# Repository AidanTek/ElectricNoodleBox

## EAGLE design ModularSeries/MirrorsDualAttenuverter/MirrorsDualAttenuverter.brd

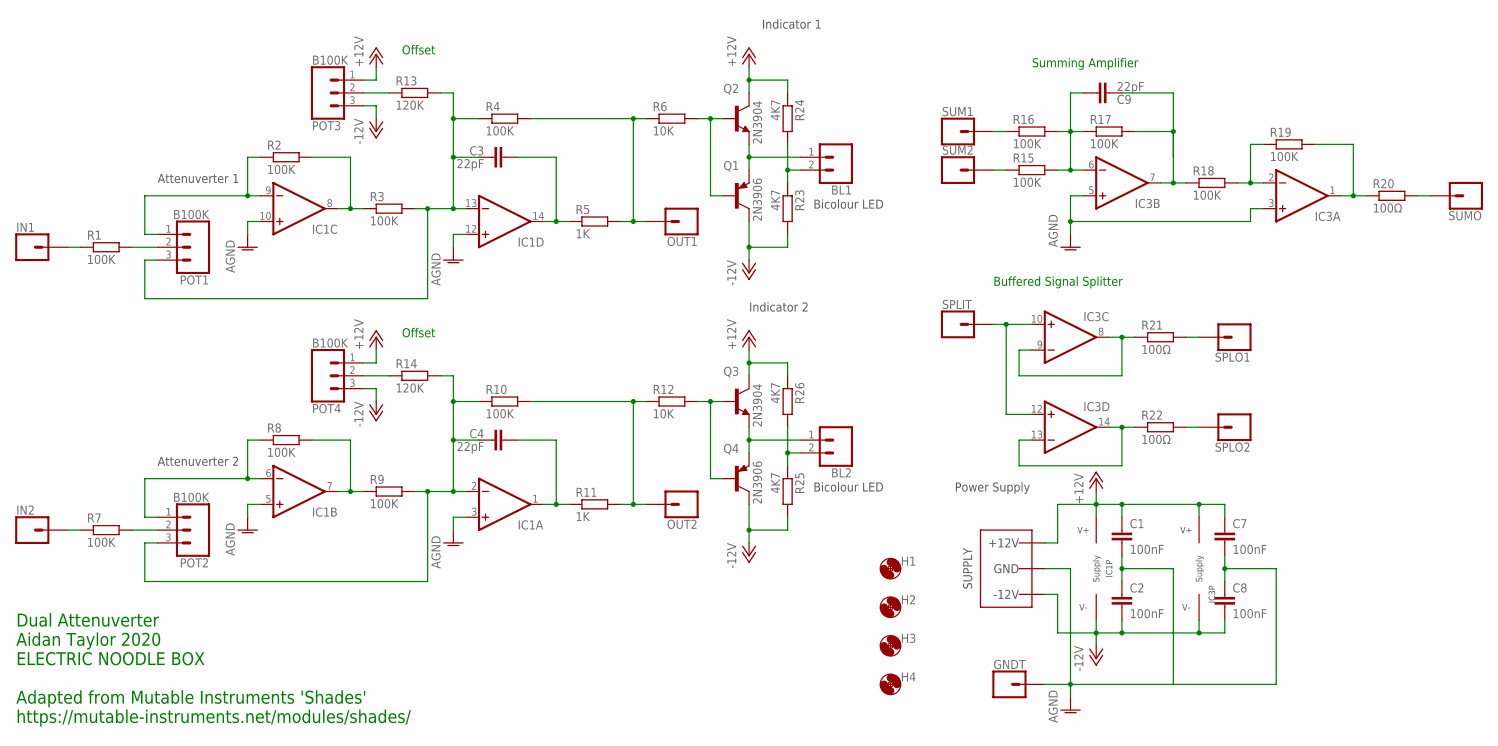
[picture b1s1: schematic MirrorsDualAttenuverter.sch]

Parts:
BL1, BL2: 2XWIREPAD; 1X02
C1, C2, C7, C8: 100nF; C050-025X075
C3, C4, C9: 22pF; C050-025X075
GNDT: 1XWIREPAD; 1X01
H1, H2, H3, H4: MOUNT-HOLE3.2; 3,2
IC1, IC3: TL0X4DIL; DIL14
IN1, IN2: 1XWIREPAD; 1X01
OUT1, OUT2: 1XWIREPAD; 1X01
POT1, POT2, POT3, POT4: B100K; 1X03
Q1, Q4: 2N3906; TO92
Q2, Q3: 2N3904; TO92
R1, R2, R3, R4, R7, R8, R9, R10, R15, R16, R17, R18, R19: 100K; 0207/10
R5, R11: 1K; 0207/10
R6, R12: 10K; 0207/10
R13, R14: 120K; 0207/10
R20, R21, R22: 100Ω; 0207/10
R23, R24, R25, R26: 4K7; 0207/10
SPLIT: 1XWIREPAD; 1X01
SPLO1, SPLO2: 1XWIREPAD; 1X01
SUM1, SUM2: 1XWIREPAD; 1X01
SUMO: 1XWIREPAD; 1X01
WP1: COMBO_SUPPLY_HEADER; COMBINED_POWER

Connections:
+12V: C1.1, C7.1, IC1.4 (V+), IC3.4 (V+), POT3.1, POT4.1, Q2.1 (C), Q3.1 (C), R24.1, R26.1, WP1.V+1 (V++), WP1.V+2 (V++), WP1.V+3 (V++)
-12V: C2.2, C8.2, IC1.11 (V-), IC3.11 (V-), POT3.3, POT4.3, Q1.1 (C), Q4.1 (C), R23.2, R25.2, WP1.V-1 (V--), WP1.V-2 (V--), WP1.V-3 (V--)
AGND: C1.2, C2.1, C7.2, C8.1, GNDT.1, IC1.3 (+IN), IC1.5 (+IN), IC1.10 (+IN), IC1.12 (+IN), IC3.3 (+IN), IC3.5 (+IN), WP1.GND1 (AGND), WP1.GND2 (AGND), WP1.GND3 (AGND), WP1.GND4 (AGND), WP1.GND5 (AGND), WP1.GND6 (AGND), WP1.GND7 (AGND), WP1.GND8 (AGND)
unnamed: POT1.2, R1.2
unnamed: IC1.9 (-IN), POT1.1, R2.1
unnamed: POT2.2, R7.2
unnamed: IC1.8 (OUT), R2.2, R3.1
unnamed: C3.1, IC1.13 (-IN), POT1.3, R3.2, R4.1, R13.2
unnamed: OUT1.1, R4.2, R5.2, R6.1
unnamed: C3.2, IC1.14 (OUT), R5.1
unnamed: Q1.2 (B), Q2.2 (B), R6.2
unnamed: IN1.1, R1.1
unnamed: IC3.2 (-IN), R18.2, R19.1
unnamed: IC1.6 (-IN), POT2.1, R8.1
unnamed: IC1.7 (OUT), R8.2, R9.1
unnamed: C4.1, IC1.2 (-IN), POT2.3, R9.2, R10.1, R14.2
unnamed: OUT2.1, R10.2, R11.2, R12.1
unnamed: C4.2, IC1.1 (OUT), R11.1
unnamed: IN2.1, R7.1
unnamed: Q3.2 (B), Q4.2 (B), R12.2
unnamed: BL2.1, Q3.3 (E), Q4.3 (E)
unnamed: BL1.1, Q1.3 (E), Q2.3 (E)
unnamed: POT3.2, R13.1
unnamed: C9.2, IC3.6 (-IN), R15.2, R16.2, R17.1
unnamed: POT4.2, R14.1
unnamed: C9.1, IC3.7 (OUT), R17.2, R18.1
unnamed: IC3.1 (OUT), R19.2, R20.1
unnamed: R20.2, SUMO.1
unnamed: R16.1, SUM1.1
unnamed: R15.1, SUM2.1
unnamed: IC3.8 (OUT), IC3.9 (-IN), R21.1
unnamed: IC3.13 (-IN), IC3.14 (OUT), R22.1
unnamed: IC3.10 (+IN), IC3.12 (+IN), SPLIT.1
unnamed: R21.2, SPLO1.1
unnamed: R22.2, SPLO2.1
unnamed: BL1.2, R23.1, R24.2
unnamed: BL2.2, R25.1, R26.2

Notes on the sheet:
Power Supply
Attenuverter 1
Attenuverter 2
Indicator 1
Indicator 2
Bicolour LED
Dual Attenuverter Aidan Taylor 2020 ELECTRIC NOODLE BOX Adapted from Mutable Instruments 'Shades' https://mutable-instruments.net/modules/shades/
Offset
Summing Amplifier
Buffered Signal Splitter

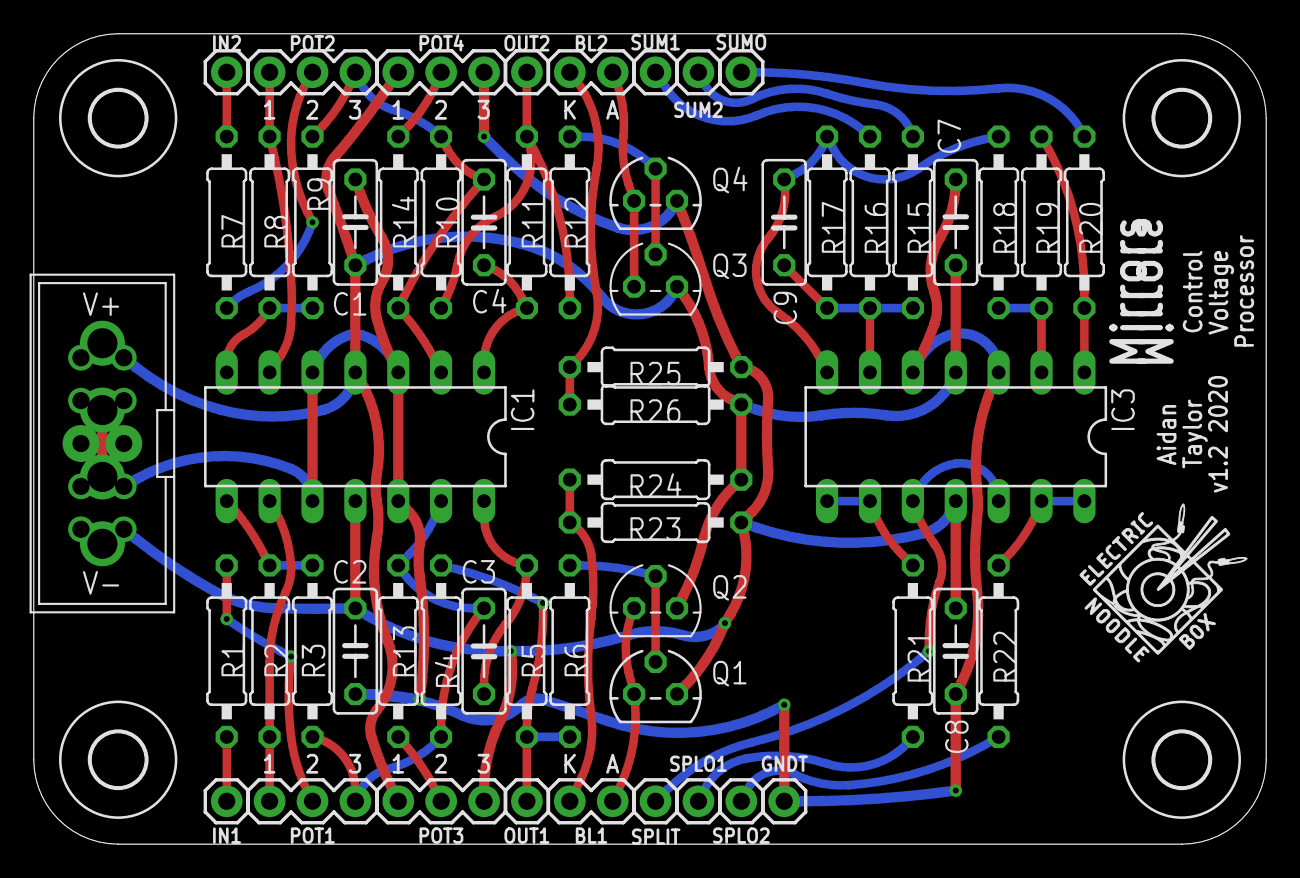
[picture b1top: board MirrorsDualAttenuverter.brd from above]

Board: 2 copper layers, 73.0 x 48.0 mm, 63 parts (1 on the bottom side), 37 nets.

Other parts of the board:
U$1, U$2: LOGO10X10

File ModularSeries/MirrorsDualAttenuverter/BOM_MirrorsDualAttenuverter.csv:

"Qty";"Value";"Device";"Package";"Parts";"Description";"POPULARITY";"SPICEPREFIX";
"2";"";"TL0X4DIL";"DIL14";"IC1, IC3";"";"";"";
"15";"100K";"R-EU_0207/10";"0207/10";"R1, R2, R3, R4, R7, R8, R9, R10, R13, R14, R15, R16, R17, R18, R19";"RESISTOR, European symbol";"81";"R";
"6";"100nF";"C-EU050-025X075";"C050-025X075";"C1, C2, C5, C6, C7, C8";"CAPACITOR, European symbol";"29";"C";
"3";"100Ω";"R-EU_0207/10";"0207/10";"R20, R21, R22";"RESISTOR, European symbol";"81";"R";
"4";"1K";"R-EU_0207/10";"0207/10";"R5, R6, R11, R12";"RESISTOR, European symbol";"81";"R";
"11";"1XWIREPAD";"1XWIREPAD";"1X01";"GNDT, IN1, IN2, OUT1, OUT2, SPLIT, SPLO1, SPLO2, SUM1, SUM2, SUMO";"";"";"";
"3";"22pF";"C-EU050-025X075";"C050-025X075";"C3, C4, C9";"CAPACITOR, European symbol";"29";"C";
"2";"2XWIREPAD";"2XWIREPAD";"1X02";"BL1, BL2";"";"";"";
"4";"B100K";"3XWIREPAD";"1X03";"POT1, POT2, POT3, POT4";"";"";"";
"1";"COMBO_SUPPLY_HEADER";"COMBO_SUPPLY_HEADER";"COMBINED_POWER";"WP1";"";"";"";
"1";"LM358";"LM358";"DIL08";"IC2";"";"";"";
"4";"MOUNT-HOLE3.2";"MOUNT-HOLE3.2";"3,2";"H1, H2, H3, H4";"MOUNTING HOLE with drill center marker";"7";"";

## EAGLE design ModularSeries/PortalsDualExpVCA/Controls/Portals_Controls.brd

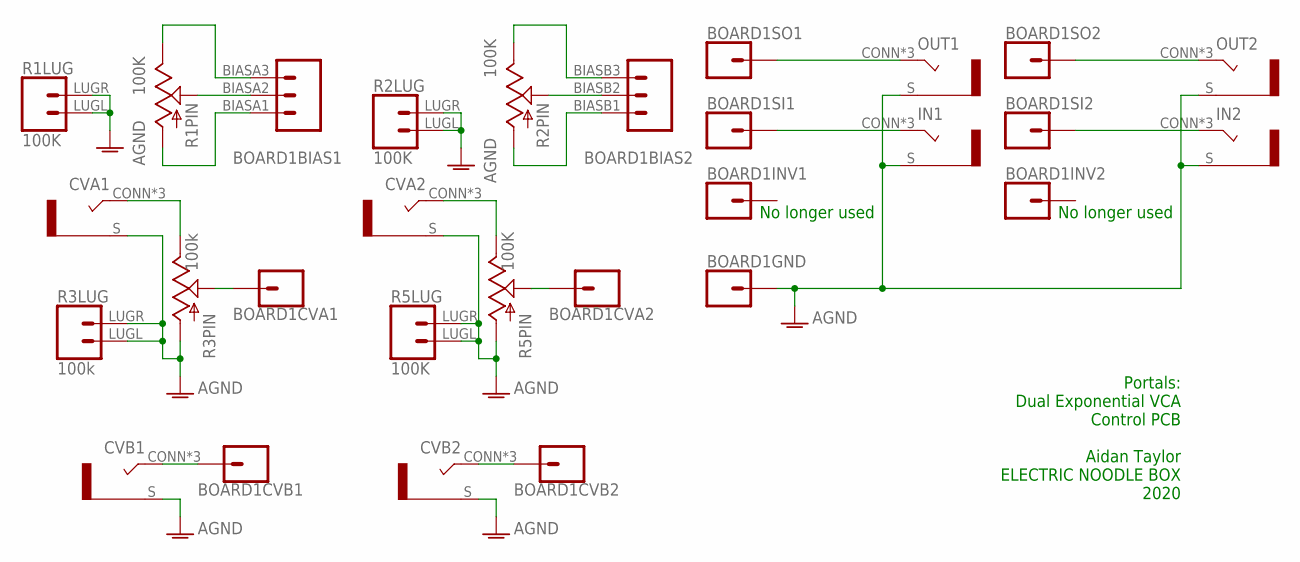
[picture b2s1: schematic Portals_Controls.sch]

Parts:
BOARD1: PORTALS_LINK; PORTALS
CVA1, CVA2: COMBI-JACKCINCHNANA; NEWCOMBOJACK_PANEL
CVB1, CVB2: COMBI-JACKCINCHNANA; NEWCOMBOJACK_PANEL
IN1, IN2: COMBI-JACKCINCHNANA; NEWCOMBOJACK_PANEL
OUT1, OUT2: COMBI-JACKCINCHNANA; NEWCOMBOJACK_PANEL
R1, R2, R5: 100K; ALPHA_RV09_9MMPOT
R3: 100k; ALPHA_RV09_9MMPOT

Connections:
AGND: BOARD1.G1 (1), BOARD1.G2 (1), BOARD1.G3 (1), BOARD1.G4 (1), CVA1.S, CVA2.S, CVB1.S, CVB2.S, IN1.S, IN2.S, OUT1.S, OUT2.S, R1.LUGL (1), R1.LUGR (2), R2.LUGL (1), R2.LUGR (2), R3.C1 (A), R3.LUGL (1), R3.LUGR (2), R5.C1 (A), R5.LUGL (1), R5.LUGR (2)
unnamed: BOARD1.CVA2 (1), CVB1.CONN (T), CVB1.T1 (T), CVB1.T2 (T)
unnamed: BOARD1.CVIB2 (1), CVB2.CONN (T), CVB2.T1 (T), CVB2.T2 (T)
unnamed: CVA1.CONN (T), CVA1.T1 (T), CVA1.T2 (T), R3.C3 (B)
unnamed: BOARD1.CVA1 (1), R3.C2 (W)
unnamed: BOARD1.BIASA2 (2), R1.C2 (W)
unnamed: BOARD1.BIASA1 (1), R1.C1 (A)
unnamed: BOARD1.BIASA3 (3), R1.C3 (B)
unnamed: BOARD1.SOA (1), OUT1.CONN (T), OUT1.T1 (T), OUT1.T2 (T)
unnamed: BOARD1.SIA (1), IN1.CONN (T), IN1.T1 (T), IN1.T2 (T)
unnamed: BOARD1.SIB (1), IN2.CONN (T), IN2.T1 (T), IN2.T2 (T)
unnamed: CVA2.CONN (T), CVA2.T1 (T), CVA2.T2 (T), R5.C3 (B)
unnamed: BOARD1.CVIB1 (1), R5.C2 (W)
unnamed: BOARD1.BIASB1 (1), R2.C1 (A)
unnamed: BOARD1.BIASB2 (2), R2.C2 (W)
unnamed: BOARD1.BIASB3 (3), R2.C3 (B)
unnamed: BOARD1.SOB (1), OUT2.CONN (T), OUT2.T1 (T), OUT2.T2 (T)

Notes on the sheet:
Portals: Dual Exponential VCA Control PCB Aidan Taylor ELECTRIC NOODLE BOX 2020
No longer used

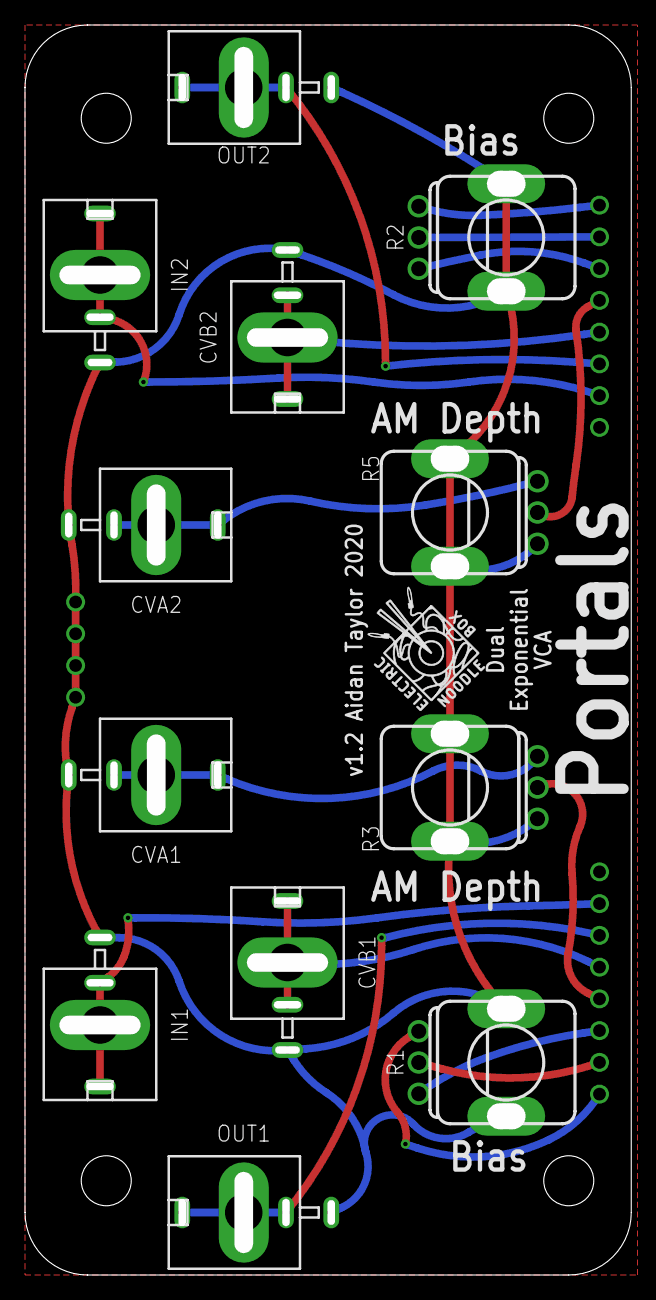
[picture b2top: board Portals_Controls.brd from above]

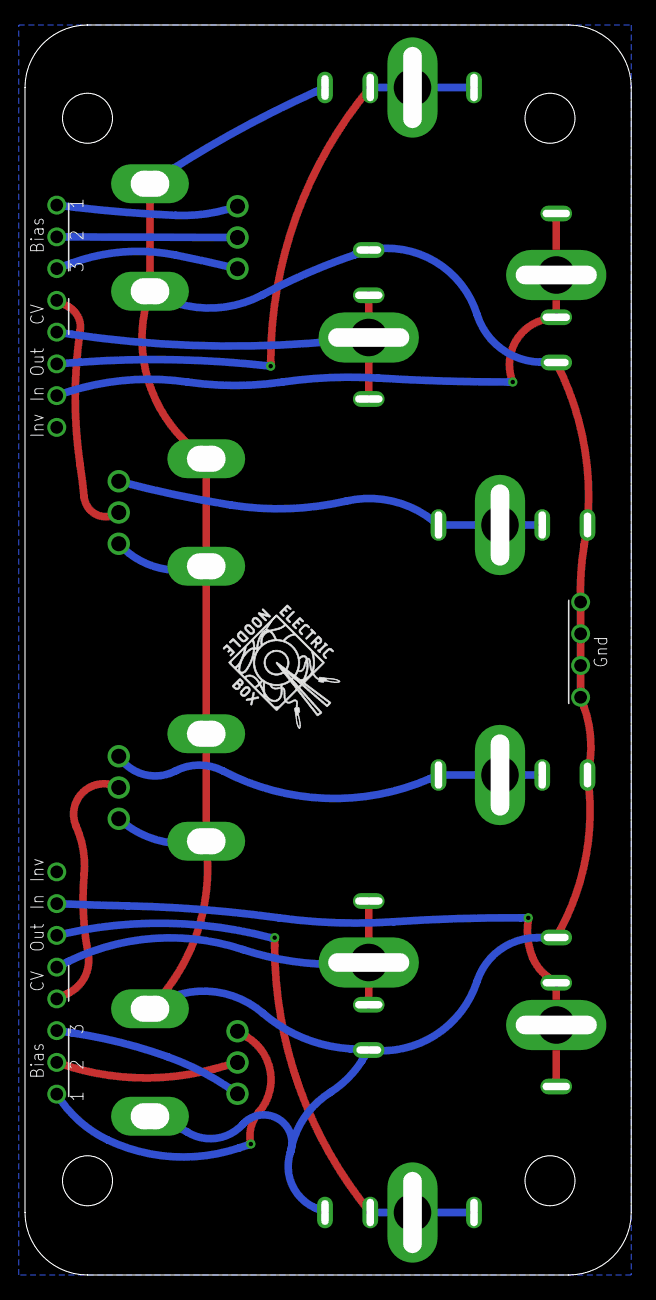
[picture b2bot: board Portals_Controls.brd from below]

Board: 2 copper layers, 48.5 x 100.0 mm, 15 parts (2 on the bottom side), 17 nets.

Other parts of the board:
U$1, U$2: LOGO10X10

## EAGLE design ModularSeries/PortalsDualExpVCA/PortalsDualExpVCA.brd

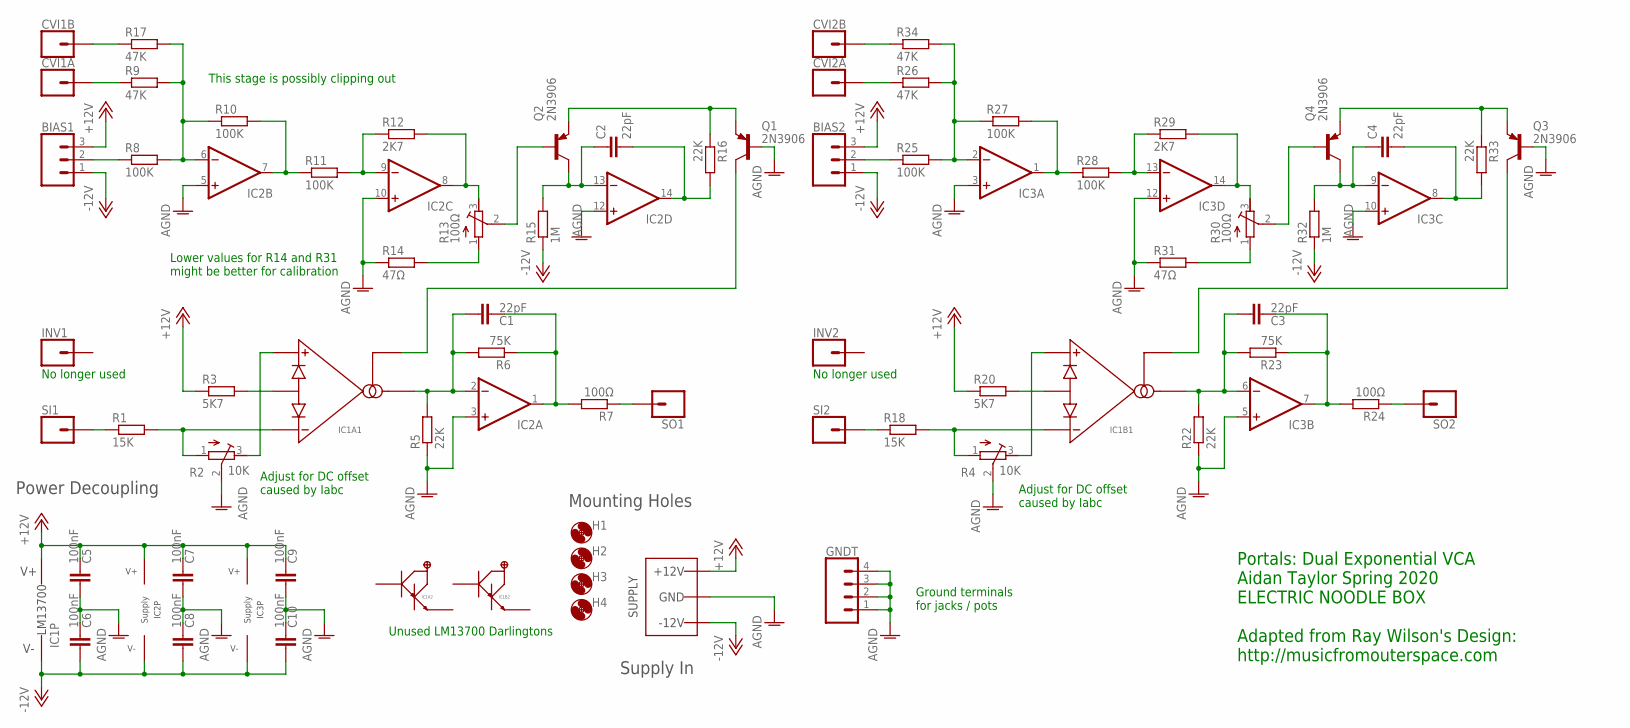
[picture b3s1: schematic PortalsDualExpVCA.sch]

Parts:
BIAS1, BIAS2: 3XWIREPAD; 1X03
C1, C2, C3, C4: 22pF; C050-025X075
C5, C6, C7, C8, C9, C10: 100nF; C050-025X075
CVI1A, CVI1B, CVI2A, CVI2B: 1XWIREPAD; 1X01
GNDT: 4XWIREPAD; 1X04
H1, H2, H3, H4: MOUNT-HOLE3.2; 3,2
IC1: LM13700DIL; DIL16
IC2, IC3: TL0X4DIL; DIL14
INV1, INV2: 1XWIREPAD; 1X01
Q1, Q2, Q3, Q4: 2N3906; TO92
R1, R18: 15K; 0207/10
R2, R4: 10K; RTRIM3296W
R3, R20: 5K7; 0207/10
R5, R16, R22, R33: 22K; 0207/10
R6, R23: 75K; 0207/10
R7, R24: 100Ω; 0207/10
R8, R10, R11, R25, R27, R28: 100K; 0207/10
R9, R17, R26, R34: 47K; 0207/10
R12, R29: 2K7; 0207/10
R13, R30: 100Ω; RTRIM3296W
R14, R31: 47Ω; 0207/10
R15, R32: 1M; 0207/10
SI1, SI2: 1XWIREPAD; 1X01
SO1, SO2: 1XWIREPAD; 1X01
WP1: COMBO_SUPPLY_HEADER; COMBINED_POWER

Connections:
+12V: BIAS1.3, BIAS2.3, C5.2, C7.2, C9.2, IC1.11 (V+), IC2.4 (V+), IC3.4 (V+), R3.1, R20.1, WP1.V+1 (V++), WP1.V+2 (V++), WP1.V+3 (V++)
-12V: BIAS1.1, BIAS2.1, C6.1, C8.1, C10.1, IC1.6 (V-), IC2.11 (V-), IC3.11 (V-), R15.1, R32.1, WP1.V-1 (V--), WP1.V-2 (V--), WP1.V-3 (V--)
AGND: C5.1, C6.2, C7.1, C8.2, C9.1, C10.2, GNDT.1, GNDT.2, GNDT.3, GNDT.4, IC2.3 (+IN), IC2.5 (+IN), IC2.10 (+IN), IC2.12 (+IN), IC3.3 (+IN), IC3.5 (+IN), IC3.10 (+IN), IC3.12 (+IN), Q1.2 (B), Q3.2 (B), R2.2 (S), R4.2 (S), R5.1, R14.1, R22.1, R31.1, WP1.GND1 (AGND), WP1.GND2 (AGND), WP1.GND3 (AGND), WP1.GND4 (AGND), WP1.GND5 (AGND), WP1.GND6 (AGND), WP1.GND7 (AGND), WP1.GND8 (AGND)
unnamed: R1.1, SI1.1
unnamed: IC1.3 (AMP+), R2.3 (E)
unnamed: BIAS1.2, R8.1
unnamed: IC1.4 (AMP-), R1.2, R2.1 (A)
unnamed: IC1.2 (DIODES), R3.2
unnamed: R7.1, SO1.1
unnamed: C1.1, IC1.5 (AMPOUT), IC2.2 (-IN), R5.2, R6.2
unnamed: C1.2, IC2.1 (OUT), R6.1, R7.2
unnamed: CVI1A.1, R9.1
unnamed: IC2.6 (-IN), R8.2, R9.2, R10.1, R17.2
unnamed: IC2.7 (OUT), R10.2, R11.1
unnamed: IC2.9 (-IN), R11.2, R12.1
unnamed: IC2.8 (OUT), R12.2, R13.3 (E)
unnamed: R13.1 (A), R14.2
unnamed: Q2.2 (B), R13.2 (S)
unnamed: C2.1, IC2.13 (-IN), Q2.1 (C), R15.2
unnamed: Q1.3 (E), Q2.3 (E), R16.1
unnamed: C2.2, IC2.14 (OUT), R16.2
unnamed: CVI1B.1, R17.1
unnamed: IC1.1 (AMPBIAS), Q1.1 (C)
unnamed: R18.1, SI2.1
unnamed: IC1.14 (AMP+), R4.3 (E)
unnamed: IC1.13 (AMP-), R4.1 (A), R18.2
unnamed: IC1.15 (DIODES), R20.2
unnamed: C3.1, IC1.12 (AMPOUT), IC3.6 (-IN), R22.2, R23.2
unnamed: C3.2, IC3.7 (OUT), R23.1, R24.2
unnamed: R24.1, SO2.1
unnamed: BIAS2.2, R25.1
unnamed: CVI2A.1, R26.1
unnamed: IC3.2 (-IN), R25.2, R26.2, R27.1, R34.2
unnamed: IC3.1 (OUT), R27.2, R28.1
unnamed: IC3.13 (-IN), R28.2, R29.1
unnamed: IC3.14 (OUT), R29.2, R30.3 (E)
unnamed: R30.1 (A), R31.2
unnamed: C4.1, IC3.9 (-IN), Q4.1 (C), R32.2
unnamed: C4.2, IC3.8 (OUT), R33.2
unnamed: Q3.3 (E), Q4.3 (E), R33.1
unnamed: IC1.16 (AMPBIAS), Q3.1 (C)
unnamed: Q4.2 (B), R30.2 (S)
unnamed: CVI2B.1, R34.1

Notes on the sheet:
Portals: Dual Exponential VCA Aidan Taylor Spring 2020 ELECTRIC NOODLE BOX Adapted from Ray Wilson's Design: http://musicfromouterspace.com
Mounting Holes
Power Decoupling
Supply In
Unused LM13700 Darlingtons
Ground terminals for jacks / pots
Lower values for R14 and R31 might be better for calibration
This stage is possibly clipping out
No longer used
Adjust for DC offset caused by Iabc

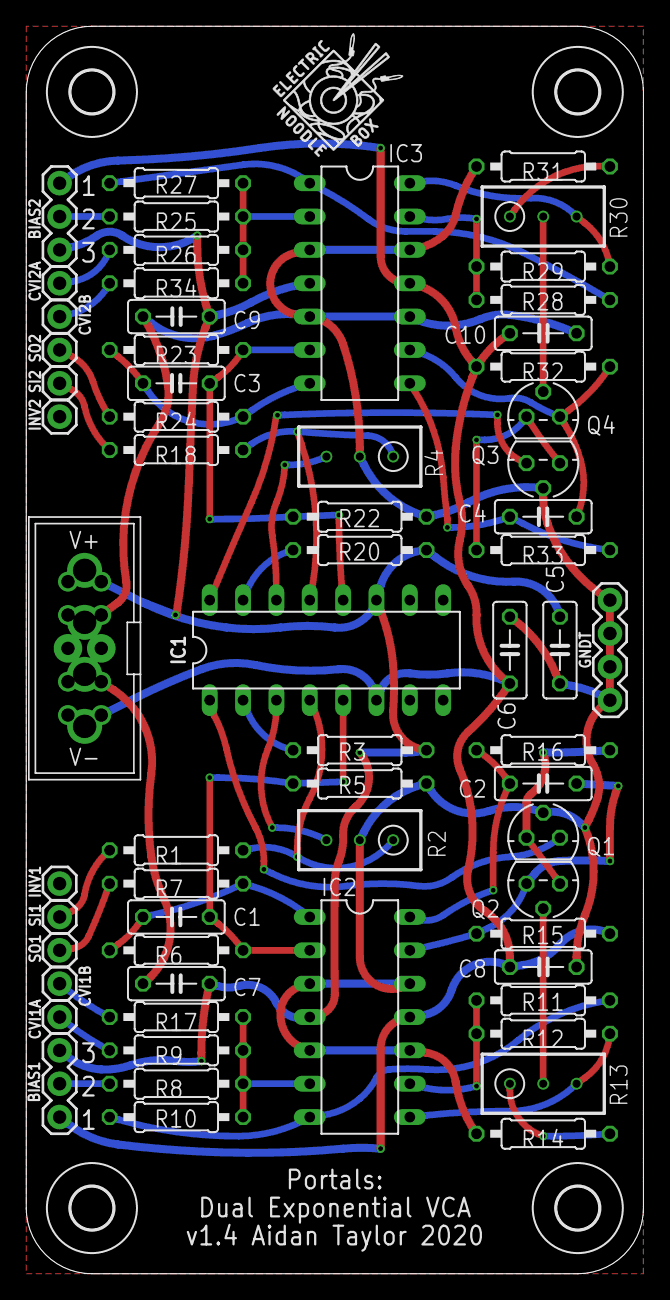
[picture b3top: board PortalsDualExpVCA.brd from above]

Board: 2 copper layers, 47.0 x 95.0 mm, 69 parts (1 on the bottom side), 43 nets.

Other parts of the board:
U$1, U$2: LOGO10X10

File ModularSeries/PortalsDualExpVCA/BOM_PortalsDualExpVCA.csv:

Qty,Value,Package,Parts,Description,Retailer,Catalogue
,,,,,,
6,100K,0207/10,"R8, R10, R11, R25, R27, R28",RESISTOR 1/4W,Farnell,2329853
2,100Ω,0207/10,"R7, R24",RESISTOR 1/4W,Farnell,2329854
4,1K,0207/10,"R2, R4, R19, R21",RESISTOR 1/4W,Farnell,2329885
2,1M,0207/10,"R15, R32",RESISTOR 1/4W,Farnell,2329894
4,15K,0207/10,"R1, R18, R35, R36", RESISTOR 1/4W, Farnell,2329873
4,22K,0207/10,"R5, R16, R22, R33",RESISTOR 1/4W,Farnell,2329901
2,2K7,0207/10,"R12, R29",RESISTOR 1/4W,Farnell,2329914
4,47K,0207/10,"R9, R17, R26, R34",RESISTOR 1/4W,Farnell,2329944
2,47Ω,0207/10,"R14, R31",RESISTOR 1/4W,Farnell,2329945
2,5K6,0207/10,"R3, R20",RESISTOR 1/4W,Farnell,2329958
2,75K,0207/10,"R6, R23",RESISTOR 1/4W,Farnell,2329972
2,100Ω,RTRIM3296W,"R13, R30",Trimm resistor,Farnell,9353186
,,,,,,
6,100nF,C050-025X075,"C5, C6, C7, C8, C9, C10",CAPACITOR,Farnell,2797801
4,22pF,C050-025X075,"C1, C2, C3, C4",CAPACITOR,Farnell,1457695
,,,,,,
4,2N3906,TO92,"Q1, Q2, Q3, Q4",PNP Transistor,Farnell,1574372
1,LM13700_DIP,DIL16,IC1,LM13700 16 pin DIL,Farnell,3118206
2,TL084_DIP,DIL14,"IC2, IC3",TL084 14 pin DIL,Farnell,3117825
,,,,,,
1,Power Header,,WP1,4 way MTA156 or 10 way IDC,Farnell,589068
1,(Alt) Power Header,,WP1,10 way Shrouded IDC,Farnell,2843527
,,,,,,
10,Banana Connector,,"CVI1A, CVI1B, CVI2A, CVI2B, INV1, INV2, SI1, SI2, SO1, SO2",Banana or Jack patch point (panel part),Farnell,1698951
2,B100K,,"BIAS1, BIAS2",Taiwan Alpha 16mm (panel part),Rapid,65-0756
4,B10K,,"CVI1A, CVI1B, CVI2A, CVI2B",Taiwan Alpha 16mm (panel part),Rapid,65-0753
2,SPDT,,"INV1, INV2, SI1, SI2", SPDT Toggle Switch, Farnell,9473416

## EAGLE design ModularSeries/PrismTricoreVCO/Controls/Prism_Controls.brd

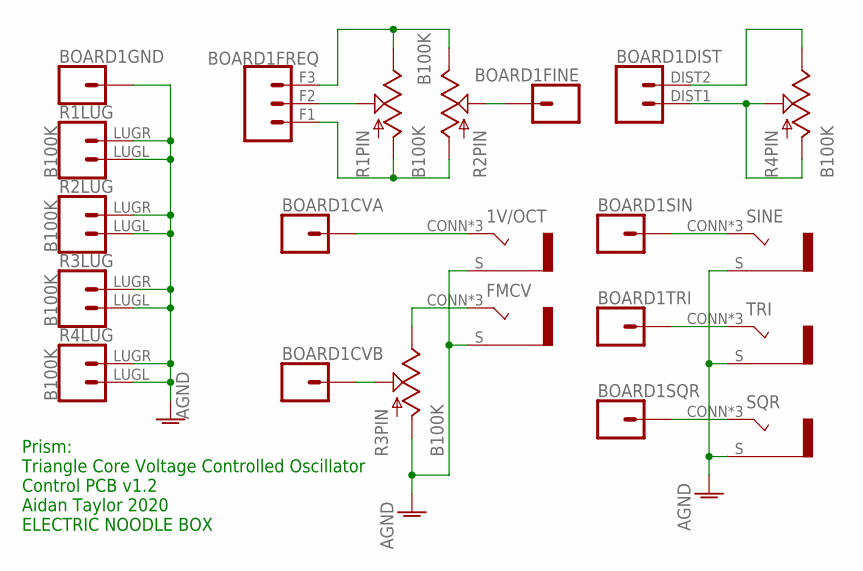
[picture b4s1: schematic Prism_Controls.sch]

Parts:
1V/OCT: COMBI-JACKCINCHNANA; NEWCOMBOJACK_PANEL
BOARD1: PRISM_LINK; PRISM
FMCV: COMBI-JACKCINCHNANA; NEWCOMBOJACK_PANEL
R1, R2, R3, R4: B100K; ALPHA_RV09_9MMPOT
SINE: COMBI-JACKCINCHNANA; NEWCOMBOJACK_PANEL
SQR: COMBI-JACKCINCHNANA; NEWCOMBOJACK_PANEL
TRI: COMBI-JACKCINCHNANA; NEWCOMBOJACK_PANEL

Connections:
AGND: 1V/OCT.S, BOARD1.GNDA (1), BOARD1.GNDB (1), FMCV.S, R1.LUGL (1), R1.LUGR (2), R2.LUGL (1), R2.LUGR (2), R3.C1 (A), R3.LUGL (1), R3.LUGR (2), R4.LUGL (1), R4.LUGR (2), SINE.S, SQR.S, TRI.S
unnamed: 1V/OCT.CONN (T), 1V/OCT.T1 (T), 1V/OCT.T2 (T), BOARD1.CVA (1)
unnamed: BOARD1.F1 (1), R1.C1 (A), R2.C1 (A)
unnamed: BOARD1.F3 (3), R1.C3 (B), R2.C3 (B)
unnamed: BOARD1.F2 (2), R1.C2 (W)
unnamed: BOARD1.FINE (1), R2.C2 (W)
unnamed: FMCV.CONN (T), FMCV.T1 (T), FMCV.T2 (T), R3.C3 (B)
unnamed: BOARD1.CVB (1), R3.C2 (W)
unnamed: BOARD1.DIST1 (1), R4.C1 (A), R4.C2 (W)
unnamed: BOARD1.DIST2 (2), R4.C3 (B)
unnamed: BOARD1.SIN (1), SINE.CONN (T), SINE.T1 (T), SINE.T2 (T)
unnamed: BOARD1.TRI (1), TRI.CONN (T), TRI.T1 (T), TRI.T2 (T)
unnamed: BOARD1.SQR (1), SQR.CONN (T), SQR.T1 (T), SQR.T2 (T)

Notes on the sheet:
Prism: Triangle Core Voltage Controlled Oscillator Control PCB v1.2 Aidan Taylor 2020 ELECTRIC NOODLE BOX

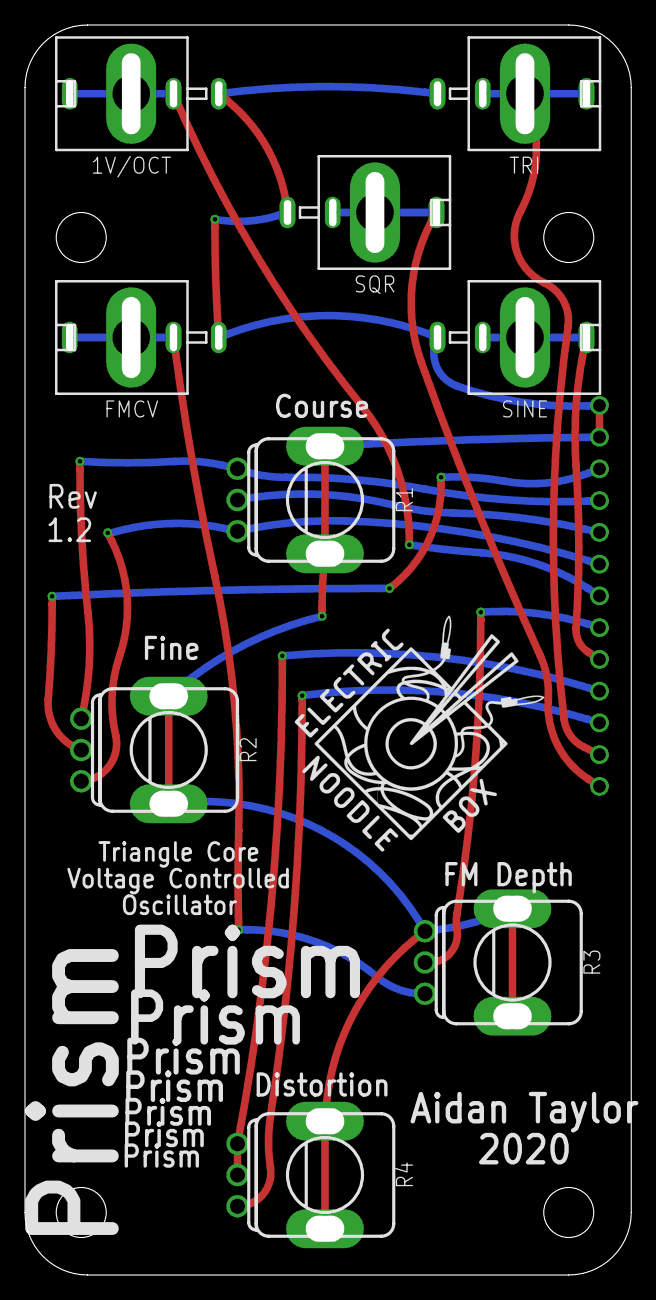
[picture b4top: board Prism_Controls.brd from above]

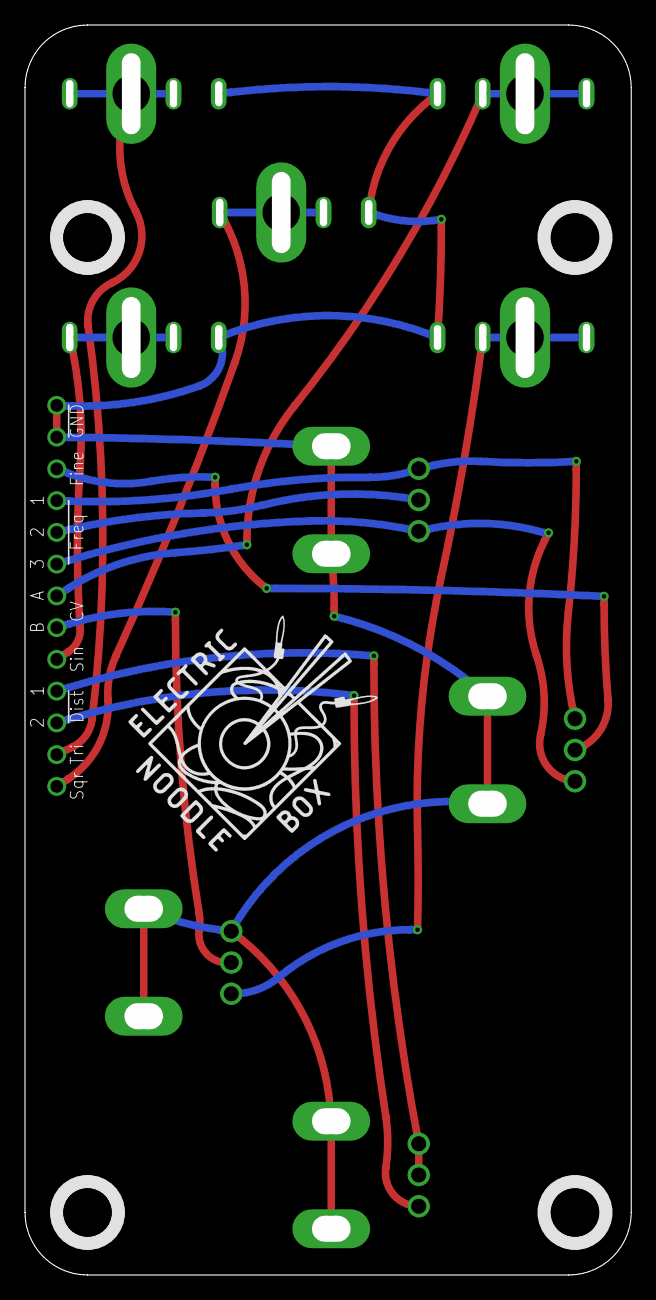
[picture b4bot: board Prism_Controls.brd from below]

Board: 2 copper layers, 48.5 x 100.0 mm, 12 parts (2 on the bottom side), 13 nets.

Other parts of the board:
U$1, U$2: LOGO20X20
